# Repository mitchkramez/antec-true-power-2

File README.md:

# Antec TP-II 550 Recap + Truecontrol 2.0 Control Panel Bypass

The Antec TP-II 550 is a powerful power supply that was originally offered in two variants: one with the TrueControl panel and one without. The TrueControl panel was a unique feature that mounted in a 5.25" drive bay and provided manual voltage adjustment through four potentiometers (pots) for the 12V, 5V, 3.3V, and fan voltage rails.

If you have the Truecontrol 2.0 version without the control panel—or if you've lost the original panel—you may have noticed a significant problem: the power supply defaults to voltages that are barely within ATX specification, with all rails running quite low. This makes the PSU difficult to use reliably without the control panel.

Fortunately, with some community help and reverse engineering, it's possible to build a simple replacement control circuit that restores full functionality to this beast of a power supply. This guide will walk you through creating your own TrueControl replacement using readily available components.

---

## Credits

This project was made possible thanks to the collaborative efforts of several community members:

- **@zigzagjoe** and **@mmu_man** — Identified the connector type used by the TrueControl panel
- **Mr. Cacodemon** (Power Supply Central Discord) — Provided PCB photos, pinouts, and pot measurements from an actual control panel and the caps list

---

## Recapping

Before you begin, these are almost guaranteed to need to be recapped. Below is the list of caps you'll need. I've also created a [Digikey list](https://www.digikey.com/en/mylists/list/2HG381A1MP), but it's missing the fan daughterboard cap that's usually just fine.

**General Recapping Notes:**

1. Original brands used will vary but will always be the same spec. For example the 22uf 50v is a Fuhjyyu TN instead of Koshin KRM, or the 4700uf 10v are Teapo SC instead of Fuhjyyu TM.
2. The list only applies to the non-EU models. EU models with APFC use a different platform from CWT that is the same other than the primary side which has APFC circuitry, so many of the smaller value caps will likely be different or placed in different spots.
3. See the recapping map attached to this post if you need it! This map is the same for all non-EU Truepower 2.0 Models.

| Caps (Orig → Recommended Replacement) | Notes | Qty |
|---|---|---|
| 4700uf 10v Fuhjyyu TM → 4700uf 6.3v Rubycon ZLQ | 10mm diameter | 4 |
| 3300uf 16v Fuhjyyu TM → 3300uf 16v Elite ED | These generally don't go bad, but Elite brand caps are hard to find. Two alternatives are in the Digikey list depending on what's in stock. One is 12.5mm (Panasonic FM) diameter so it'll be a tight fit but still work. Originals were 10mm. | 2 |
| 1000uf 10v Fuhjyyu TN → 1000uf 10v Rubycon ZLH | | 2 |
| 470uf 25v Fuhjyyu TN → 470uf 25v Rubycon ZLH | | 1 |
| 220uf 16v Koshin KRM → 220uf 16v Rubycon YXJ | | 1 |
| 47uf 35v Fuhjyyu TN → 47uf 35v Rubycon YXM | Chemicon LE is the equivalent if the YXM isn't in stock (any general purpose cap will work) | 1 |
| 22uf 50v Koshin KRM → 22uf 50v Rubycon YXM | Chemicon LE is the equivalent if the YXM isn't in stock (any general purpose cap will work) | 1 |
| 10uf 50v Fuhjyyu TN → 10uf 50v Rubycon YXM | Chemicon LE is the equivalent if the YXM isn't in stock (any general purpose cap will work) | 2 |
| 10uf 16v Koshin KRJ → 10uf 16v Kemet ESS | Fan daughterboard, 4x7mm | 1 |
| 1uf 50v Fuhjyyu TN → 1uf 50v Rubycon YXM | Chemicon LE is the equivalent if the YXM isn't in stock (any general purpose cap will work) | 2 |

---

## TrueControl 2.0 Bypass

### What You'll Need

**3296W Potentiometers (1/2 watt or 1/4 watt):**
- 12V rail: 4–600Ω pot (1kΩ pot works well)
- 3.3V rail: 4–1500Ω pot (2kΩ pot works well)
- 5V rail: 4–1500Ω pot (2kΩ pot works well)
- Fan line: 5400–5600Ω pot (5kΩ pot works well)
- [Example pots on Amazon](https://www.amazon.com/dp/B0CM6PJV5T)

**Connector:**
- Molex PicoBlade (0533980667) 6pin connector (available from [DigiKey](https://www.digikey.com/en/products/detail/molex/0533980667/5116074) or Amazon)
- [Amazon bundle option](https://www.amazon.com/dp/B0CL9NMVXS)

**Optional:**
- 330Ω - 4.7kΩ 805 SMD resistor for LEDs (if you want a power indicator light, resistance will depend on your brightness tolerance and color choice.)
- 3mm 5v through hole LED

---

### TrueControl Pinout

| Wire Color | Function |
|---|---|
| Yellow | 12V |
| Brown | 3.3V |
| Black | Ground (Vgnd) |
| Red | 5V |
| Green | Vcc (LED power only) |
| Blue | Fan |

---

### Assembly Instructions

**Step 1: Prepare the Potentiometers**

For each of the four potentiometers:
1. Identify pins 1, 2, and 3 on the pot
2. Connect pins 1 and 2 together — these will be your common ground connection
3. Pin 3 will be your voltage adjustment output

**Step 2: Wire to the Connector**
1. Connect the joined pins 1 & 2 from all four pots to the Black (Ground) wire on the connector
2. Connect pin 3 of each pot to its corresponding wire:
   - 12V pot → Yellow wire
   - 3.3V pot → Brown wire
   - 5V pot → Red wire
   - Fan pot → Blue wire
   - The Green (Vcc) wire is only needed if you're adding LED indicators

**Step 3: Test and Adjust**
1. Connect your assembled control circuit to the power supply connector
2. Use your BIOS readings or a multimeter to check voltages
3. Adjust each potentiometer until voltages and fan are set to preference:
   - Voltages: The 5v, 3.3v, and 12v knobs allows individual adjustment of voltages even while the system is running, without interrupting system functions. With this functionality you can stabilize a heavily loaded system, even when overclocking. (Note: you can only adjust within ATX spec (±5%) (the psu will keep within ±1-3% of set voltages). The PSU has UVP (under voltage protection) and OVP (over voltage protection), so even if you do somehow go out of allowed range it'll shut off. 
   - Fan: The fan knob allows adjustment of minimum speed of internal PSU fan as well as case fans connected to Fan Only connectors. (Note: this adjusts the fan speed to temp curve, this is why adjusting the knob will appear to not do much when the psu is cool)

**Step 4: Mounting**

For a temporary solution, hot glue the assembly directly to the power supply casing. A PCB design is also included in this repository for a more permanent solution.

---

While this may not be as elegant as the original TrueControl panel, it's a functional and cost-effective way to restore your Antec TP-II 550 w/ Truecontrol to full working order. The total cost in components is minimal, and the assembly is straightforward enough for anyone comfortable with basic soldering.

Happy building, and enjoy your newly functional power supply!

---

## General Notes on the TruePower Line

The Antec TruePower 2.0 line was a high-end set of models released in 2005 to replace the original TruePower line. The TruePower 2.0 had four different versions:

- **Standard models** available in 4 wattages: TPII-380, TPII-430, TPII-480, TPII-550
  *(APFC EU models: TPII-380P, TPII-430P, TPII-480P, TPII-550P)*
- **EPS12V model** for server use: TP2-550EPS12V *(APFC EU model: TP2-550PEPS12V)* — the only 2.0 model with dual fans like the original TruePower models
- **TRUE Blue 2.0 model**: TPII-480 Blue *(APFC EU model: TPII-480P Blue)* — same as the standard 480W model but with a clear fan and blue LEDs
- **TRUE Control 2.0 model**: TPII-550 Control *(APFC EU model: TPII-550P Control)* — TPII-550 with a 5.25" bay control panel for fine voltage adjustment for overclocking and fan speed override control

---

---

*Original post by mitchkramez on [TinkerDifferent](https://tinkerdifferent.com/threads/antec-tp-ii-550-recap-truecontrol-2-0-control-panel-bypass.5222/)*

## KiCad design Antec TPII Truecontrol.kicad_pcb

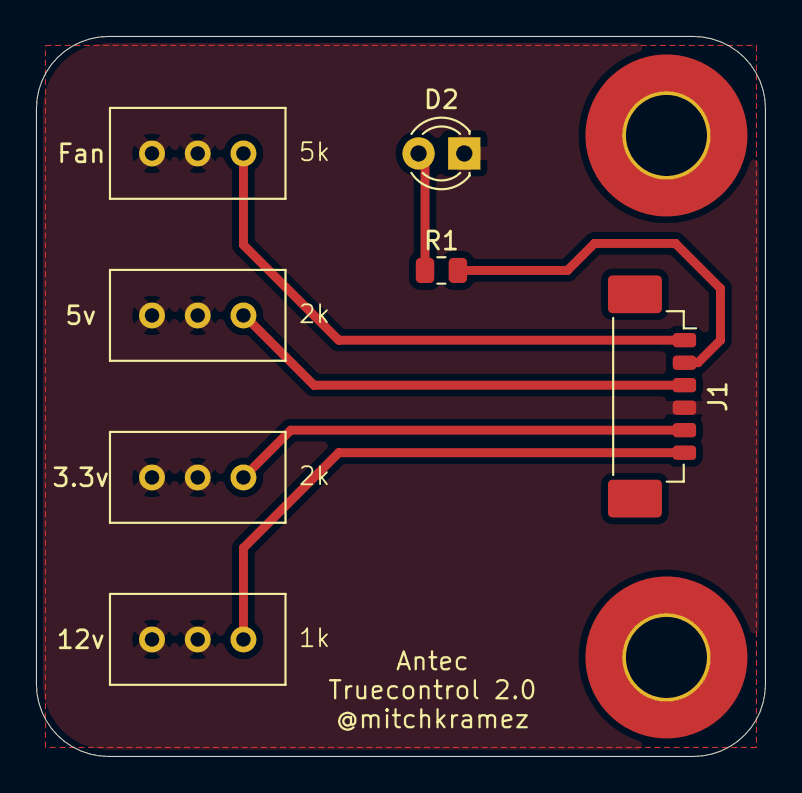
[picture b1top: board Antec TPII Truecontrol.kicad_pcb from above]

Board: 2 copper layers, 40.5 x 40.0 mm, 7 parts (0 on the bottom side), 7 nets.

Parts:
3.3v, 5v: 2k; Potentiometer_Bourns_3296W_Vertical
12v: 1K; Potentiometer_Bourns_3296W_Vertical
D2: LED; LED_D3.0mm
Fan: 5k; Potentiometer_Bourns_3296W_Vertical
J1: Conn_01x06_Socket; Molex_PicoBlade_53398-0671_1x06-1MP_P1.25mm_Vertical
R1: 330; R_0805_2012Metric

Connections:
GND: 3.3v.1, 3.3v.2, 5v.1, 5v.2, 12v.1, 12v.2, D2.1 (K), Fan.1, Fan.2, J1.4
unnamed: D2.2 (A), R1.1
unnamed: Fan.3, J1.1
unnamed: J1.2, R1.2
unnamed: 5v.3, J1.3
unnamed: 3.3v.3, J1.5
unnamed: 12v.3, J1.6

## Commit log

2026-04-26 Update README for Truecontrol 2.0 version clarification
2026-04-26 Revise adjustment instructions for PSU settings
    Updated instructions for adjusting voltages and fan settings in the power supply unit. Clarified functionality and safety features related to adjustments.
